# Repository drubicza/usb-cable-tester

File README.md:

# USB Cable Tester

Just a simple USB cable tester based on a tweet by [aroerina2](https://twitter.com/aroerina2/status/802435032325328896/video/1) with added USB-A and USB-B socket.

Board Schematic
---

Board Layout
---

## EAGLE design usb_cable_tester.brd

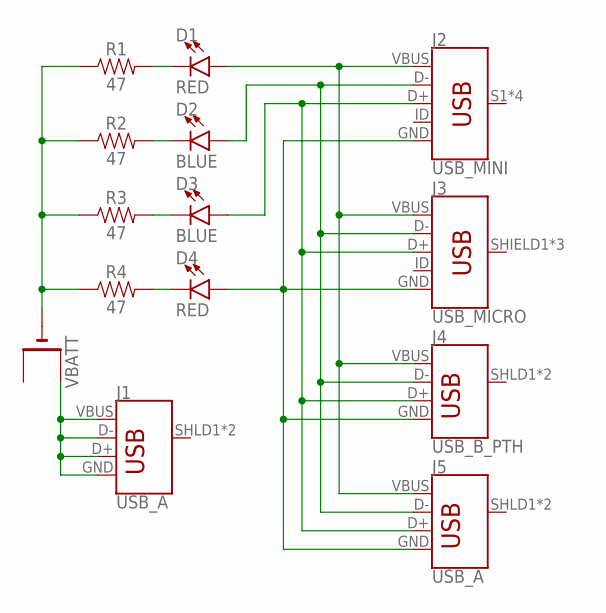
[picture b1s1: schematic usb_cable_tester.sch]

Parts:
D1, D4: RED; LED-0603
D2, D3: BLUE; LED-0603
J1, J5: USB_A; USB-A-S-NOSILK-FEMALE
J2: USB_MINI; USB-MINIB
J3: USB_MICRO; USB-B-MICRO-SMD
J4: USB_B_PTH; USB-B-PTH
R1, R2, R3, R4: 47; 0603
VBATT: CR2032SMT; CR2032-SMD

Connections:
GND: R1.1, R2.1, R3.1, R4.1, VBATT.-
unnamed: D1.C, R1.2
unnamed: D2.C, R2.2
unnamed: D3.C, R3.2
unnamed: D4.C, R4.2
unnamed: J1.D+, J1.D-, J1.GND, J1.VBUS, VBATT.+$1 (+)
unnamed: D1.A, J2.VBUS, J3.VBUS, J4.VBUS, J5.VBUS
unnamed: D2.A, J2.D-, J3.D-, J4.D-, J5.D-
unnamed: D3.A, J2.D+, J3.D+, J4.D+, J5.D+
unnamed: D4.A, J2.GND, J3.GND, J4.GND, J5.GND

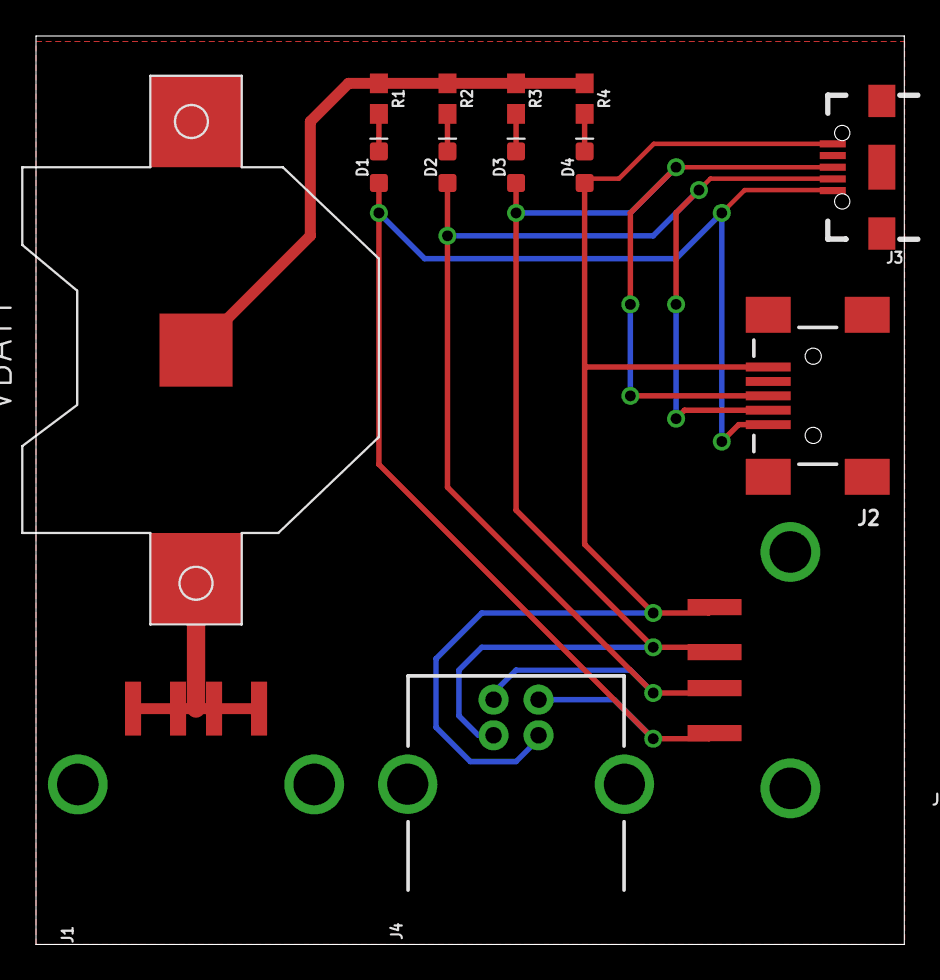
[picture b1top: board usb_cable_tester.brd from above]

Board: 2 copper layers, 48.2 x 50.5 mm, 14 parts (0 on the bottom side), 10 nets.

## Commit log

2017-02-24 Initial commit :octocat:

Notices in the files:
parts and their libraries:
SparkFun-LED: Licensing: Creative Commons ShareAlike 4.0 International - https://creativecommons.org/licenses/by-sa/4.0
